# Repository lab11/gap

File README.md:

GAP: Generic Access Point
=========================
<div align="center">

</div>

GAP is the WiFi router for low-power and embedded Internet of Things devices.
While WiFi routers provide ubiquitous Internet access for laptops and
smartphones, GAP provides Internet access for low-power sensors and wearable
devices. It supports both 802.15.4 and Bluetooth Low Energy.

GAP is implemented as a cape for the
[BeagleBone Black](http://beagleboard.org/black). It uses two TI CC2520 radios
and a Nordic nRF51822 radio to provide connectivity. Each radio has a linux
kernel module to allow userspace access to the radios.

Hardware
--------

The GAP cape features a SPI interface to two CC2520
radios, one of which is amplified with a CC2591, and one nRF51822 radio.
It also includes four LEDs.

Software
--------

The CC2520 radios are
[supported natively](https://github.com/torvalds/linux/blob/master/drivers/net/ieee802154/cc2520.c)
in newer versions of the Linux kernel (>=4.1).

The nRF51822 BLE radio is a work-in-progress. It can be used as a standalone
BLE radio (see [this repo](https://github.com/lab11/nrf5x-base) for a starting
point), but does not have great integration with the BBB at this point.

Setting Up GAP
--------------

To setup a BBB to work with GAP, follow these instructions:

1. Start with a recent build of Debian for the BBB. We suggest starting
with pretty new version of Debian, like that can be found
[here](http://elinux.org/Beagleboard:BeagleBoneBlack_Debian#Jessie_Snapshot_console).

2. Once that is setup, ssh to the BBB and update the kernel to the newest
version. This will not only make sure you're running the latest code,
but also ensure all of the kernel modules will be present.

        sudo apt-get update
        sudo apt-get install vim git lsb-release
        sudo /opt/scripts/tools/update_kernel.sh --beta --bone-channel

    Luckily [Robert C Nelson](https://github.com/RobertCNelson/)
    has made this really easy with a convenient script.

3. Now we have to setup the device tree overlay to let Linux know that
the the radios exist. The GAP overlay and others are setup in a repository also
maintained by RCN.

        git clone https://github.com/lab11/bb.org-overlays
        cd bb.org-overlays
        ./dtc-overlay.sh
        ./install.sh

    That puts the compiled overlay in the correct place, now we need to tell
    the BBB to use it at boot.

        vim /boot/uEnv.txt
        # Edit that line that looks like this to include the reference to GAP
        cape_enable=bone_capemgr.enable_partno=BB-GAP

4. Reboot to apply this.

        sudo reboot

Sniffing 15.4 Packets
---------------------

To make sure everything is working, it is pretty easy to get Linux to
print out the packets the radio is receiving.

1. Install the `wpan-tools` to configure all of the 15.4 devices.

        sudo apt-get install pkg-config libnl-3-dev libnl-genl-3-dev
        wget http://wpan.cakelab.org/releases/wpan-tools-0.5.tar.gz
        tar xf wpan-tools-0.5.tar.gz
        cd wpan-tools-0.5
        ./configure
        make
        sudo make install

1. Install `tcpdump` to view the packets.

        sudo apt-get install tcpdump

2. Configure the network devices. Be sure to set the channel and PANID
to match what is transmitting the 15.4 packets.

        iwpan phy phy0 set channel 0 11
        iwpan dev wpan0 del
        iwpan phy phy0 interface add wpan0 type node c0:98:e5:00:00:00:00:01
        iwpan dev wpan0 set pan_id 0x0022
        /sbin/ifconfig wpan0 up

3. Use `tcpdump` to view them.

        sudo tcpdump -i wpan0 -vvv
        
    OR, use a simple c program to read from the raw socket.
    
        cd linux
        gcc recv_raw_802154.c -o raw
        sudo ./raw
        
    OR, use a very similar python script:
    
        cd linux
        sudo python recv_raw_802154.py

RPL Border Router
----------------

GAP can be setup as a border router running a 6LoWPAN based mesh network
with RPL as a routing layer. It uses [unstrung](https://github.com/mcr/unstrung)
to provide the RPL implementation. The rest is supported by the Linux kernel.

To set this up:

1. Setup the radios and network interfaces:

        sudo iwpan phy phy1 set channel 0 23
        sleep 15
        sudo iwpan dev wpan1 del
        sleep 15
        sudo iwpan phy phy1 interface add wpan1 type node c0:98:e5:00:00:00:00:01
        sleep 15
        sudo iwpan dev wpan1 set pan_id 0x0022
        sleep 15
        sudo ip link add link wpan1 name lowpan1 type lowpan
        sleep 15
        sudo ifconfig lowpan1 up
        sleep 15
        sudo ifconfig wpan1 up

   Note: I've found that putting a sleep between those commands makes everything run smoothly.
   Calling them too quickly seems to break things (at least in the past, it's possible
   that newer commits have solved this issue).

2. Get unstrung.

        git clone https://github.com/mcr/unstrung.git
        cd unstrung
        make

    There may be commits that need to be applied to make this
    work. Look at unstrung pull requests to see if there are
    outstanding patches that are required.

3. Run unstrung.

        /home/debian/unstrung/programs/sunshine/sunshine --verbose --dagid 0x11112222333344445555666677778888 -i lowpan1 -W 10000 --stderr -R 1 --prefix 2607:f018:800:201:c298:e588:4400:1/64 -m

4. You should be able to ping a node:

        sudo ping6 2607:f018:800:201:c298:e522:2200:bb -s 16

<!--

### Setup EEPROM

Now we are getting close. We have told Linux about the kernel modules
and added the device tree overlay to a place where Linux can find it.
The last step is to get Linux to load the overlay which will then cause
it to load the kernel modules. This is where the EEPROM comes in.

When the BeagleBone Black boots it checks for EEPROMs present on any capes
and uses the configuration data in the EEPROM to load the correct device
tree overlay.

There exists a utility to create the hexdump (data.eeprom) to flash to the
EEPROM in `/software/utility`. After creating the hexdump, apply a jumper
to the write header near the EEPROM chip and use this command to flash the
EEPROM:

Choose 12 characters to serve as the serial number, in
the form `WWYY&&&&nnnn`. From the SRM:

    WW = 2 digit week of the year of production.
    YY = 2 digit year of production.
    &&&& = Assembly code, up to you to decide.
    nnnn = incrementing board number for week of production.

After creating `data.eeprom` with the eepromflasher utilty, write it to the
cape EEPROM as root.

    # On the BBB
    sudo su
    cat data.eeprom > /sys/bus/i2c/devices/1-0057/eeprom

Where `1-0057` is the default address for the GAP cape. This can be changed
by using the solder jumper pads near the EEPROM on the upper left corner of the
board.

Unfortunately, the BBB debian distribution fails to load custom firmware from
the EEPROM on boot, and requires an capemanager configuration file to be
edited.

    sudo vim /etc/default/capemgr

    # Add this line:
    CAPE=BB-BONE-GAP

CC2520 Border Router
--------------------

One way to use the CC2520s on GAP is with the TinyOS code in a related
repo: [RaspberryPi-CC2520](https://github.com/lab11/raspberrypi-cc2520).
The `BorderRouter` application can be compiled with `make gap`.
-->

<!--

### EEPROM

The capes feature EEPROM that will allow for the BeagleBone capemgr to auto load the driver
and configure pins on boot, in accordance with the Beaglebone Black SRM. There
exists a utility to create the hexdump (data.eeprom) to flash to the EEPROM in
beaglebone-cc2520/software/utility. After creating the hexdump, apply a jumper
to the write header and use this command to flash the EEPROM:

```bash
cat data.eeprom > /sys/bus/i2c/devices/1-0057/eeprom
```

Where 1-0057 is the default address for the Zigbeag cape. This can be changed by
using the solder jumper pads on the upper left corner of the board.

Software
--------

### Install

This guide assumes the default Angstrom distro running under root.<br/>
Clone the repo to wherever you feel fit:

```bash
git clone https://github.com/lab11/beaglebone-cc2520.git
```

Note: you may have to follow the directions [here](http://derekmolloy.ie/fixing-git-and-curl-certificates-problem-on-beaglebone-blac/) to get git working correctly.

An install script is located in /software. <br/>
The script will copy the Device Tree Overlay (DTO) to /lib/firmware, and the driver to /lib/modules/KERNEL_VERSION, where KERNEL_VERSION is your current running kernel version number. <br/>
Navigate to software/ and run the install script:

```bash
cd beaglebone-cc2520/software/
./install
```

If using the Zigbeag cape with configured EEPROM, just plug it in and reboot the beaglebone and your board will be fully functional.

If EEPROM is not configured, to load the Device Tree Overlay manually:

```bash
echo BB-BONE-CC2520 > /sys/devices/bone_capemgr.9/slots
```
This command should complete with no output.
To check that the DTO has loaded, run:

```bash
cat /sys/devices/bone_capemgr.9/slots
```
Note: bone_capemgr.9 may actually be bone_capemgr.8 for different beaglebones. <br/>
You should check to see that there is now an override board in a slot after the virtual HDMI cape. <br/>
Here is my output:

```
 0: 54:PF---
 1: 55:PF---
 2: 56:PF---
 3: 57:PF---
 4: ff:P-O-L Bone-LT-eMMC-2G,00A0,Texas Instrument,BB-BONE-EMMC-2G
 5: ff:P-O-L Bone-Black-HDMI,00A0,Texas Instrument,BB-BONELT-HDMI
 7: ff:P-O-L Override Board Name,00A0,Override Manuf,BB-BONE-CC2520
```

Now that the DTO is loaded, the pins are now muxed correctly for the cc2520 board. We can now load the driver with:

```bash
modprobe cc2520
```

This command should complete with no output. <br/>
You can check that the driver loaded successfully with:

```bash
lsmod
```

#### Testing
You should now have a functioning Zigbeag cape. There are test programs located in software/driver/tests. Try running the write and read program on two beaglebones, and you should be able to see them talking to each other.

#### Install Issues
If you run into issues with any of the above commands, check dmesg for any output from the kernel. <br/>
Run this to check for issues with loading the DTO:

```bash
dmesg | grep bone_capemgr
```

Run this to check for issues with loading the driver:

```bash
dmesg | grep cc2520
```

### Kernel Module

In order to support the CC2520, you need the kernel module located in software/driver. The install script will automatically copy this into /lib/modules/KERNEL_VERSION. <br/>
This driver has been adapted from the [Linux CC2520 Driver](https:/github.com/ab500/linux-cc2520-driver). <br/>
If you would like to compile the driver from source, there is some setup involved.
I've found it easiest to use a symlink and compile from the current kernel on the Beaglebone.

```bash
opkg update
opkg upgrade
```
It would be a good idea to reboot at this point

```bash
opkg install kernel-headers
opkg install kernel-dev
cd /usr/src/kernel
make scripts
ln -s /usr/src/kernel /lib/modules/$(uname -r)/build
```

You can then navigate to beaglebone-cc2520/software/driver and run make to compile the driver. Make sure you re-run the install script, which will copy cc2520.ko to /lib/modules/KERNEL_VERSION and run depmod -a to register the driver with your system. -->

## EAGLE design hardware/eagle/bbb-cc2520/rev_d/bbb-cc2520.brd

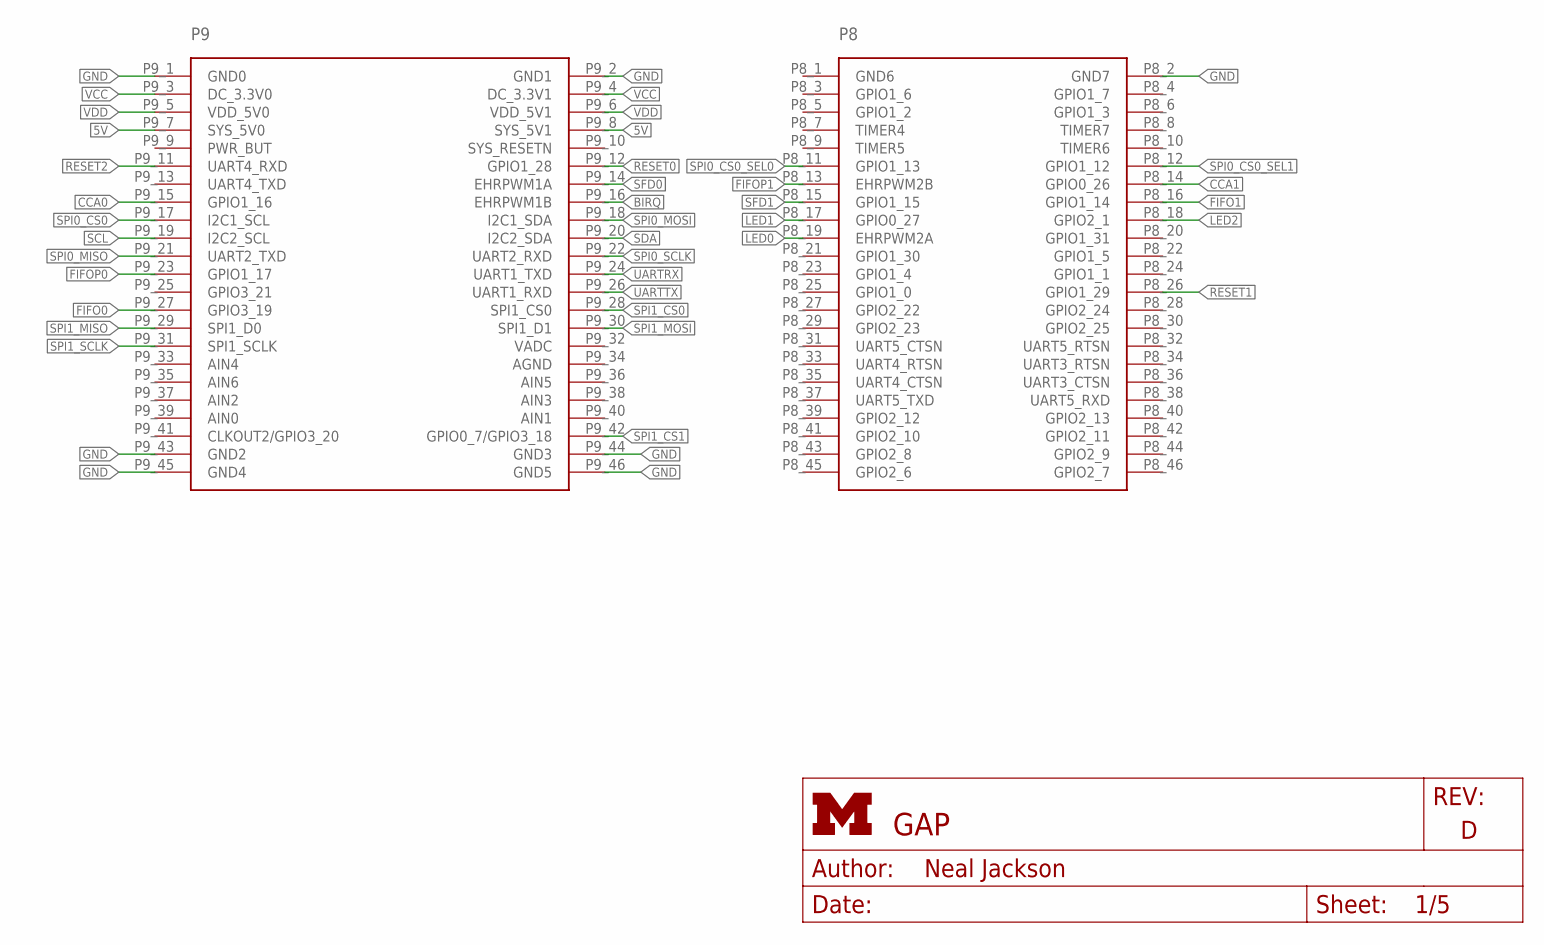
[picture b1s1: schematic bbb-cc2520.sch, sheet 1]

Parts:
P9/P8: BBB_HEADERS

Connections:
5V: P9/P8.P9_7 (SYS_5V0), P9/P8.P9_8 (SYS_5V1)
!RESET0: P9/P8.P9_12 (GPIO1_28); also elsewhere on the board
!RESET1: P9/P8.P8_26 (GPIO1_29); also elsewhere on the board
!RESET2: P9/P8.P9_11 (UART4_RXD); also elsewhere on the board
BIRQ: P9/P8.P9_16 (EHRPWM1B); also elsewhere on the board
CCA0: P9/P8.P9_15 (GPIO1_16); also elsewhere on the board
CCA1: P9/P8.P8_14 (GPIO0_26); also elsewhere on the board
FIFO0: P9/P8.P9_27 (GPIO3_19); also elsewhere on the board
FIFO1: P9/P8.P8_16 (GPIO1_14); also elsewhere on the board
FIFOP0: P9/P8.P9_23 (GPIO1_17); also elsewhere on the board
FIFOP1: P9/P8.P8_13 (EHRPWM2B); also elsewhere on the board
GND: P9/P8.P8_2 (GND7), P9/P8.P9_1 (GND0), P9/P8.P9_2 (GND1), P9/P8.P9_43 (GND2), P9/P8.P9_44 (GND3), P9/P8.P9_45 (GND4), P9/P8.P9_46 (GND5); also elsewhere on the board
LED0: P9/P8.P8_19 (EHRPWM2A); also elsewhere on the board
LED1: P9/P8.P8_17 (GPIO0_27); also elsewhere on the board
LED2: P9/P8.P8_18 (GPIO2_1); also elsewhere on the board
SCL: P9/P8.P9_19 (I2C2_SCL); also elsewhere on the board
SDA: P9/P8.P9_20 (I2C2_SDA); also elsewhere on the board
SFD0: P9/P8.P9_14 (EHRPWM1A); also elsewhere on the board
SFD1: P9/P8.P8_15 (GPIO1_15); also elsewhere on the board
SPI0_CS0: P9/P8.P9_17 (I2C1_SCL); also elsewhere on the board
SPI0_CS0_SEL0: P9/P8.P8_11 (GPIO1_13); also elsewhere on the board
SPI0_CS0_SEL1: P9/P8.P8_12 (GPIO1_12); also elsewhere on the board
SPI0_MISO: P9/P8.P9_21 (UART2_TXD); also elsewhere on the board
SPI0_MOSI: P9/P8.P9_18 (I2C1_SDA); also elsewhere on the board
SPI0_SCLK: P9/P8.P9_22 (UART2_RXD); also elsewhere on the board
SPI1_CS0: P9/P8.P9_28 (SPI1_CS0); also elsewhere on the board
SPI1_CS1: P9/P8.P9_42 (GPIO0_7/GPIO3_18); also elsewhere on the board
SPI1_MISO: P9/P8.P9_29 (SPI1_D0); also elsewhere on the board
SPI1_MOSI: P9/P8.P9_30 (SPI1_D1); also elsewhere on the board
SPI1_SCLK: P9/P8.P9_31 (SPI1_SCLK); also elsewhere on the board
UARTRX: P9/P8.P9_24 (UART1_TXD); also elsewhere on the board
UARTTX: P9/P8.P9_26 (UART1_RXD); also elsewhere on the board
VCC: P9/P8.P9_3 (DC_3.3V0), P9/P8.P9_4 (DC_3.3V1); also elsewhere on the board
VDD: P9/P8.P9_5 (VDD_5V0), P9/P8.P9_6 (VDD_5V1)

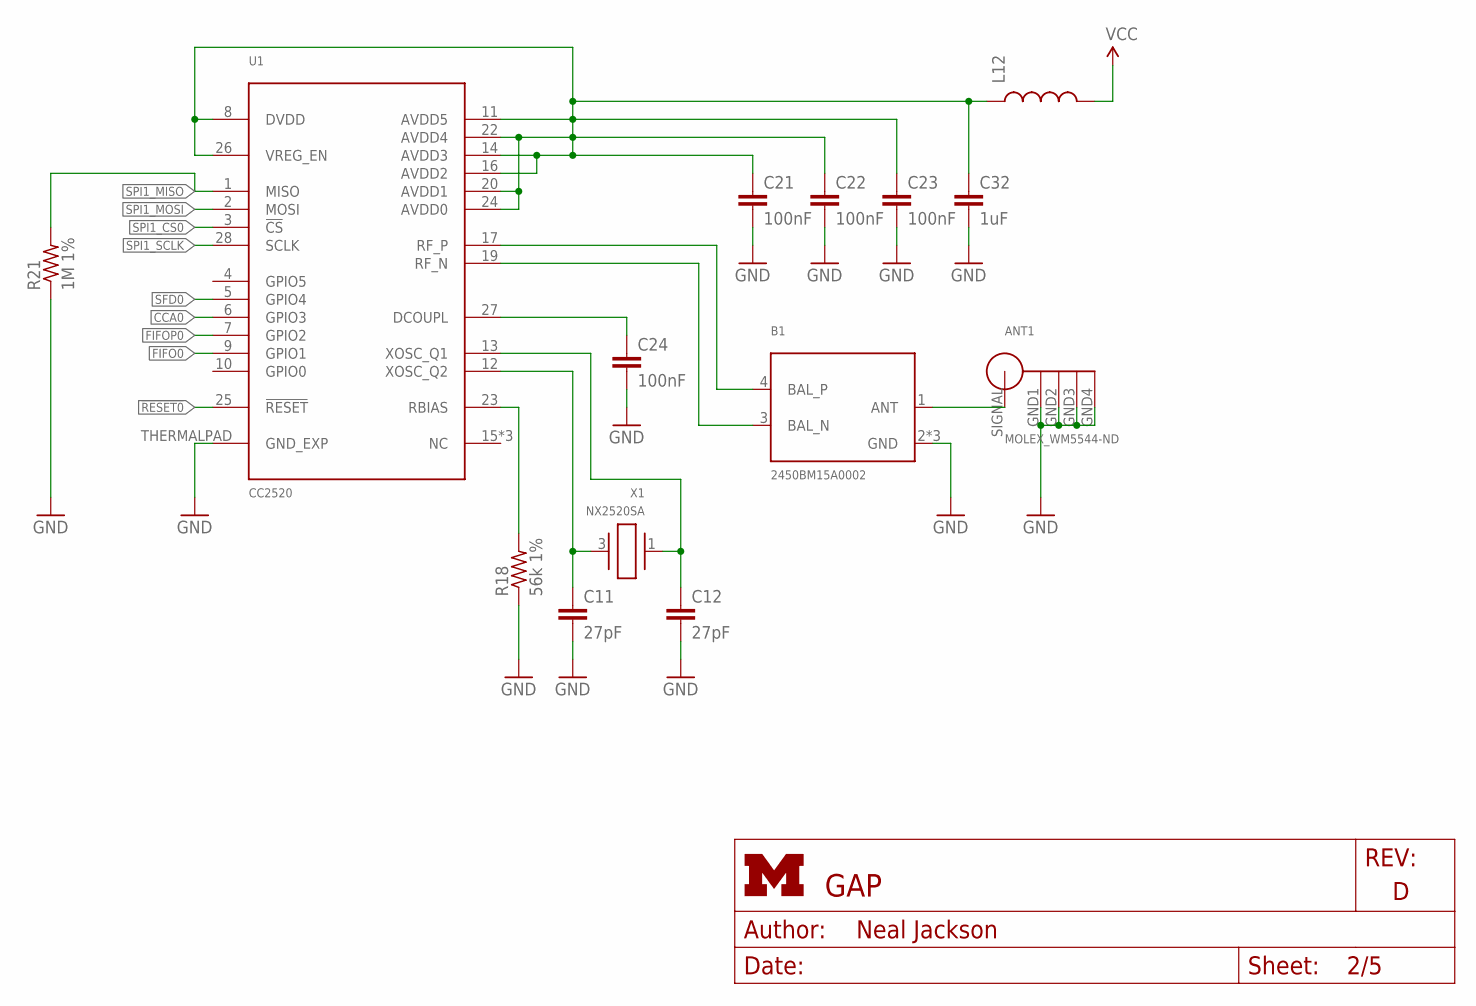
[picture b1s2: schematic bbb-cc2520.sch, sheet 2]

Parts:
ANT1: MOLEX_WM5544-ND
B1: 2450BM15A0002; 2450BM
C11, C12: 27pF; C0402; DIGIKEY 490-5869-1-ND
C21, C22, C23, C24: 100nF; C0402; DIGIKEY 490-1318-1-ND
C32: 1uF; C0603; DIGIKEY 490-1550-1-ND
L12: INDUCTOR0603; 0603; DIGIKEY 490-1015-1-ND
R18: 56k 1%; R0402; DIGIKEY P56.0KLCT-ND
R21: 1M 1%; R0402; DIGIKEY RHM1.00MCDCT-ND
U1: CC2520; S-PVQFN-N28
X1: NX2520SA

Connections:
!RESET0: U1.25 (!RESET); also elsewhere on the board
CCA0: U1.6 (GPIO3); also elsewhere on the board
FIFO0: U1.9 (GPIO1); also elsewhere on the board
FIFOP0: U1.7 (GPIO2); also elsewhere on the board
GND: ANT1.GND1, ANT1.GND2, ANT1.GND3, ANT1.GND4, B1.2 (GND), B1.5 (GND), B1.6 (GND), C11.2, C12.2, C21.2, C22.2, C23.2, C24.2, C32.2, R18.1, R21.1, U1.THERMALPAD (GND_EXP); also elsewhere on the board
unnamed: C21.1, C22.1, C23.1, C32.1, L12.1, U1.8 (DVDD), U1.11 (AVDD5), U1.14 (AVDD3), U1.16 (AVDD2), U1.20 (AVDD1), U1.22 (AVDD4), U1.24 (AVDD0), U1.26 (VREG_EN)
unnamed: ANT1.SIGNAL, B1.1 (ANT)
unnamed: C12.1, U1.13 (XOSC_Q1), X1.1
unnamed: C24.1, U1.27 (DCOUPL)
unnamed: C11.1, U1.12 (XOSC_Q2), X1.3 (2)
unnamed: R18.2, U1.23 (RBIAS)
RF_N: B1.3 (BAL_N), U1.19 (RF_N)
RF_P: B1.4 (BAL_P), U1.17 (RF_P)
SFD0: U1.5 (GPIO4); also elsewhere on the board
SPI1_CS0: U1.3 (!CS); also elsewhere on the board
SPI1_MISO: R21.2, U1.1 (MISO); also elsewhere on the board
SPI1_MOSI: U1.2 (MOSI); also elsewhere on the board
SPI1_SCLK: U1.28 (SCLK); also elsewhere on the board
VCC: L12.2; also elsewhere on the board

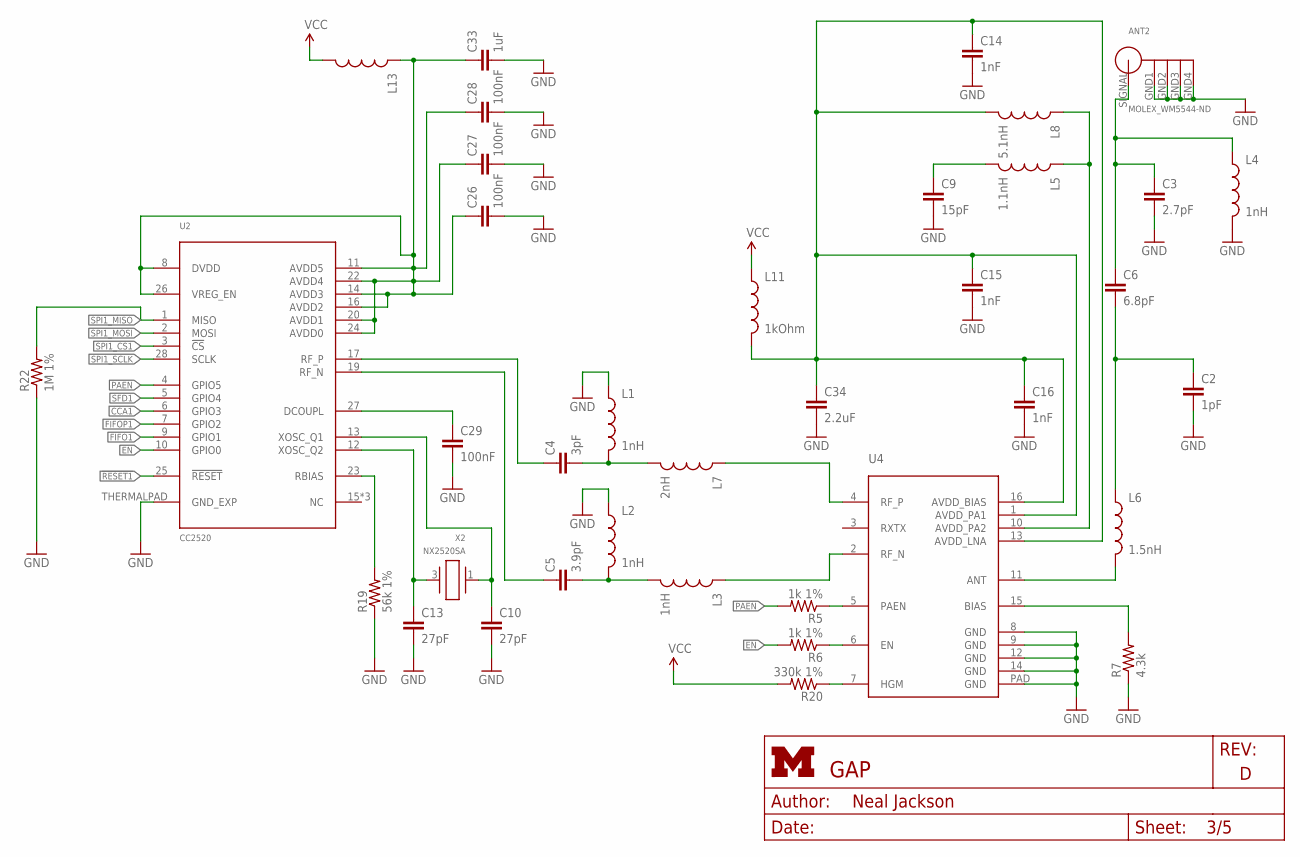
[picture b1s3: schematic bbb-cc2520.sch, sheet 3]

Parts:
ANT2: MOLEX_WM5544-ND
C2: 1pF; C0402; DIGIKEY 490-1318-1-ND
C3: 2.7pF; C0402; DIGIKEY 490-1318-1-ND
C4: 3pF; C0402; DIGIKEY 490-1318-1-ND
C5: 3.9pF; C0402; DIGIKEY 490-1318-1-ND
C6: 6.8pF; C0402; DIGIKEY 490-1318-1-ND
C9: 15pF; C0402; DIGIKEY 490-1318-1-ND
C10, C13: 27pF; C0402; DIGIKEY 490-5869-1-ND
C14, C15, C16: 1nF; C0402; DIGIKEY 490-1318-1-ND
C26, C27, C28, C29: 100nF; C0402; DIGIKEY 490-1318-1-ND
C33: 1uF; C0603; DIGIKEY 490-1550-1-ND
C34: 2.2uF; C0402; DIGIKEY 490-1318-1-ND
L1, L2, L3, L4: 1nH; C0402
L5: 1.1nH; C0402
L6: 1.5nH; C0402
L7: 2nH; C0402
L8: 5.1nH; C0402
L11: 1kOhm; C0402
L13: INDUCTOR0603; 0603; DIGIKEY 490-1015-1-ND
R5, R6: 1k 1%; R0402; DIGIKEY P56.0KLCT-ND
R7: 4.3k; R0402; DIGIKEY P56.0KLCT-ND
R19: 56k 1%; R0402; DIGIKEY P56.0KLCT-ND
R20: 330k 1%; R0402; DIGIKEY P56.0KLCT-ND
R22: 1M 1%; R0402; DIGIKEY RHM1.00MCDCT-ND
U2: CC2520; S-PVQFN-N28
U4: CC2591; PVQFN-16
X2: NX2520SA

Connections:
!RESET1: U2.25 (!RESET); also elsewhere on the board
CCA1: U2.6 (GPIO3); also elsewhere on the board
EN: R6.2, U2.10 (GPIO0)
FIFO1: U2.9 (GPIO1); also elsewhere on the board
FIFOP1: U2.7 (GPIO2); also elsewhere on the board
GND: ANT2.GND1, ANT2.GND2, ANT2.GND3, ANT2.GND4, C2.2, C3.2, C9.2, C10.2, C13.2, C14.2, C15.2, C16.2, C26.2, C27.2, C28.2, C29.2, C33.2, C34.2, L1.1, L2.1, L4.2, R7.1, R19.1, R22.1, U2.THERMALPAD (GND_EXP), U4.8 (GND), U4.9 (GND), U4.12 (GND), U4.14 (GND), U4.PAD (GND); also elsewhere on the board
unnamed: L7.1, U4.4 (RF_P)
unnamed: L3.1, U4.2 (RF_N)
unnamed: C5.2, L2.2, L3.2
unnamed: C4.2, L1.2, L7.2
unnamed: L5.1, L8.1, U4.10 (AVDD_PA2)
unnamed: C14.1, C15.1, C16.1, C34.1, L8.2, L11.2, U4.1 (AVDD_PA1), U4.13 (AVDD_LNA), U4.16 (AVDD_BIAS)
unnamed: C9.1, L5.2
unnamed: L6.2, U4.11 (ANT)
unnamed: ANT2.SIGNAL, C3.1, C6.1, L4.1
unnamed: C2.1, C6.2, L6.1
unnamed: R7.2, U4.15 (BIAS)
unnamed: R5.1, U4.5 (PAEN)
unnamed: R6.1, U4.6 (EN)
unnamed: C26.1, C27.1, C28.1, C33.1, L13.1, U2.8 (DVDD), U2.11 (AVDD5), U2.14 (AVDD3), U2.16 (AVDD2), U2.20 (AVDD1), U2.22 (AVDD4), U2.24 (AVDD0), U2.26 (VREG_EN)
unnamed: C29.1, U2.27 (DCOUPL)
unnamed: C10.1, U2.13 (XOSC_Q1), X2.1
unnamed: C13.1, U2.12 (XOSC_Q2), X2.3 (2)
unnamed: R19.2, U2.23 (RBIAS)
unnamed: R20.1, U4.7 (HGM)
PAEN: R5.2, U2.4 (GPIO5)
RF_N2: C5.1, U2.19 (RF_N)
RF_P2: C4.1, U2.17 (RF_P)
SFD1: U2.5 (GPIO4); also elsewhere on the board
SPI1_CS1: U2.3 (!CS); also elsewhere on the board
SPI1_MISO: R22.2, U2.1 (MISO); also elsewhere on the board
SPI1_MOSI: U2.2 (MOSI); also elsewhere on the board
SPI1_SCLK: U2.28 (SCLK); also elsewhere on the board
VCC: L11.1, L13.2, R20.2; also elsewhere on the board

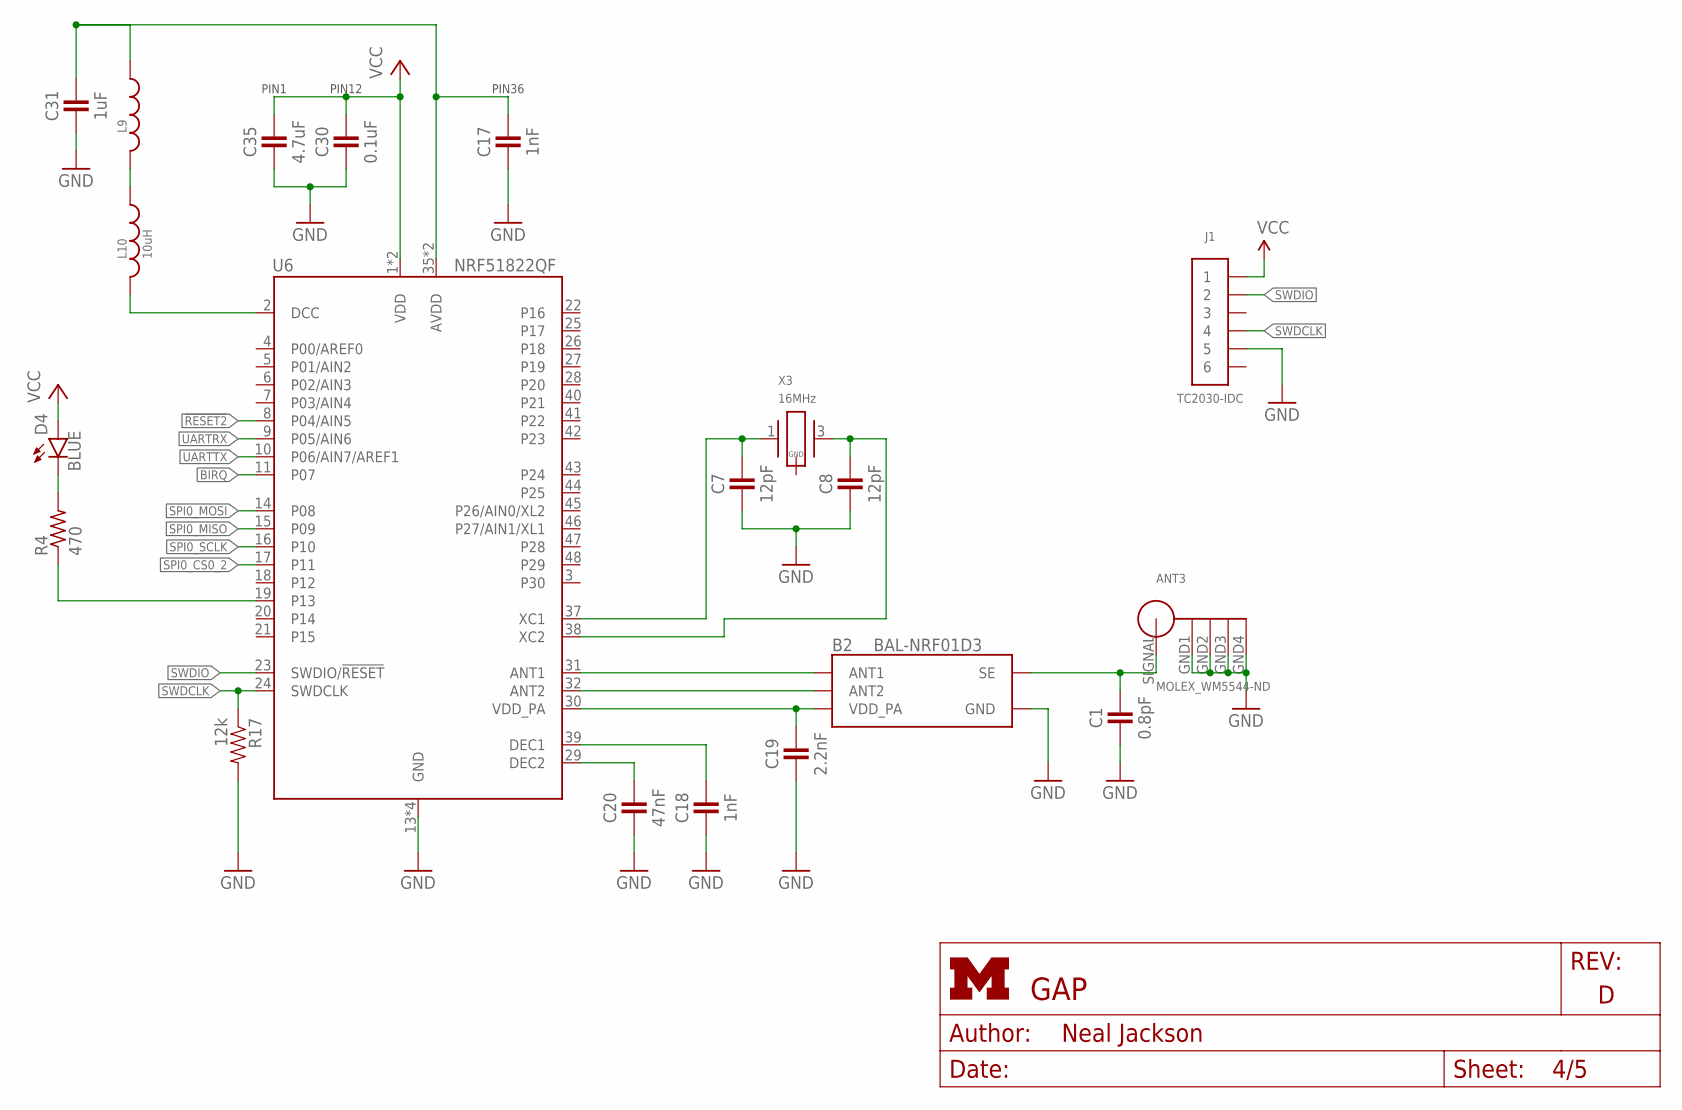
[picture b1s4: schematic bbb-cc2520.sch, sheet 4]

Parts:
ANT3: MOLEX_WM5544-ND
B2: BAL-NRF01D3
C1: 0.8pF; 0402_CAP; DIGIKEY 490-5419-1-ND
C7, C8: 12pF; 0402_CAP; DIGIKEY 490-6197-1-ND
C17, C18: 1nF; 0402_CAP; DIGIKEY 490-1303-1-ND
C19: 2.2nF; 0402_CAP; DIGIKEY 490-5419-1-ND
C20: 47nF; 0402_CAP; DIGIKEY 445-1264-1-ND
C30: 0.1uF; 0402_CAP; DIGIKEY 445-4952-1-ND
C31: 1uF; 0402_CAP; DIGIKEY 1276-1513-1-ND
C35: 4.7uF; 0402_CAP; DIGIKEY 445-5947-1-ND
D4: BLUE; LED-0603
J1: TC2030-IDC
L9: INDUCTOR0402; 0402_CAP; DIGIKEY 587-1521-1-ND
L10: 10uH; 0603_CAP; DIGIKEY 490-4025-1-ND
R4: 470; R0402; DIGIKEY RHM470JCT-ND
R17: 12k; 0603-RES; DIGIKEY RHM12.0KCDCT-ND
U6: NRF51822QF; QFN-48-6MM
X3: 16MHz; TXC-8Y; DIGIKEY 887-2003-1-ND

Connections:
!RESET2: U6.8 (P04/AIN5); also elsewhere on the board
AVDD: C17.1, C31.1, L9.1, U6.35 (AVDD), U6.36 (AVDD)
BIRQ: U6.11 (P07); also elsewhere on the board
DCC: L10.2, U6.2 (DCC)
GND: ANT3.GND1, ANT3.GND2, ANT3.GND3, ANT3.GND4, B2.GND, C1.2, C7.2, C8.2, C17.2, C18.2, C19.2, C20.2, C30.2, C31.2, C35.2, J1.5, R17.2, U6.13 (GND), U6.33 (GND), U6.34 (GND), U6.GND; also elsewhere on the board
unnamed: B2.ANT1, U6.31 (ANT1)
unnamed: B2.ANT2, U6.32 (ANT2)
unnamed: ANT3.SIGNAL, B2.SE, C1.1
unnamed: L9.2, L10.1
unnamed: C7.1, U6.37 (XC1), X3.1
unnamed: C8.1, U6.38 (XC2), X3.3 (2)
unnamed: C18.1, U6.39 (DEC1)
unnamed: C20.1, U6.29 (DEC2)
unnamed: D4.C, R4.2
unnamed: R4.1, U6.19 (P13)
SPI0_CS0_2: U6.17 (P11); also elsewhere on the board
SPI0_MISO: U6.15 (P09); also elsewhere on the board
SPI0_MOSI: U6.14 (P08); also elsewhere on the board
SPI0_SCLK: U6.16 (P10); also elsewhere on the board
SWDCLK: J1.4, R17.1, U6.24 (SWDCLK)
SWDIO: J1.2, U6.23 (SWDIO/!RESET)
UARTRX: U6.9 (P05/AIN6); also elsewhere on the board
UARTTX: U6.10 (P06/AIN7/AREF1); also elsewhere on the board
VCC: C30.1, C35.1, D4.A, J1.1, U6.1 (VDD), U6.12 (VDD); also elsewhere on the board
VDD_PA: B2.VCC (VDD_PA), C19.1, U6.30 (VDD_PA)

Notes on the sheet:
PIN12
PIN1
PIN36

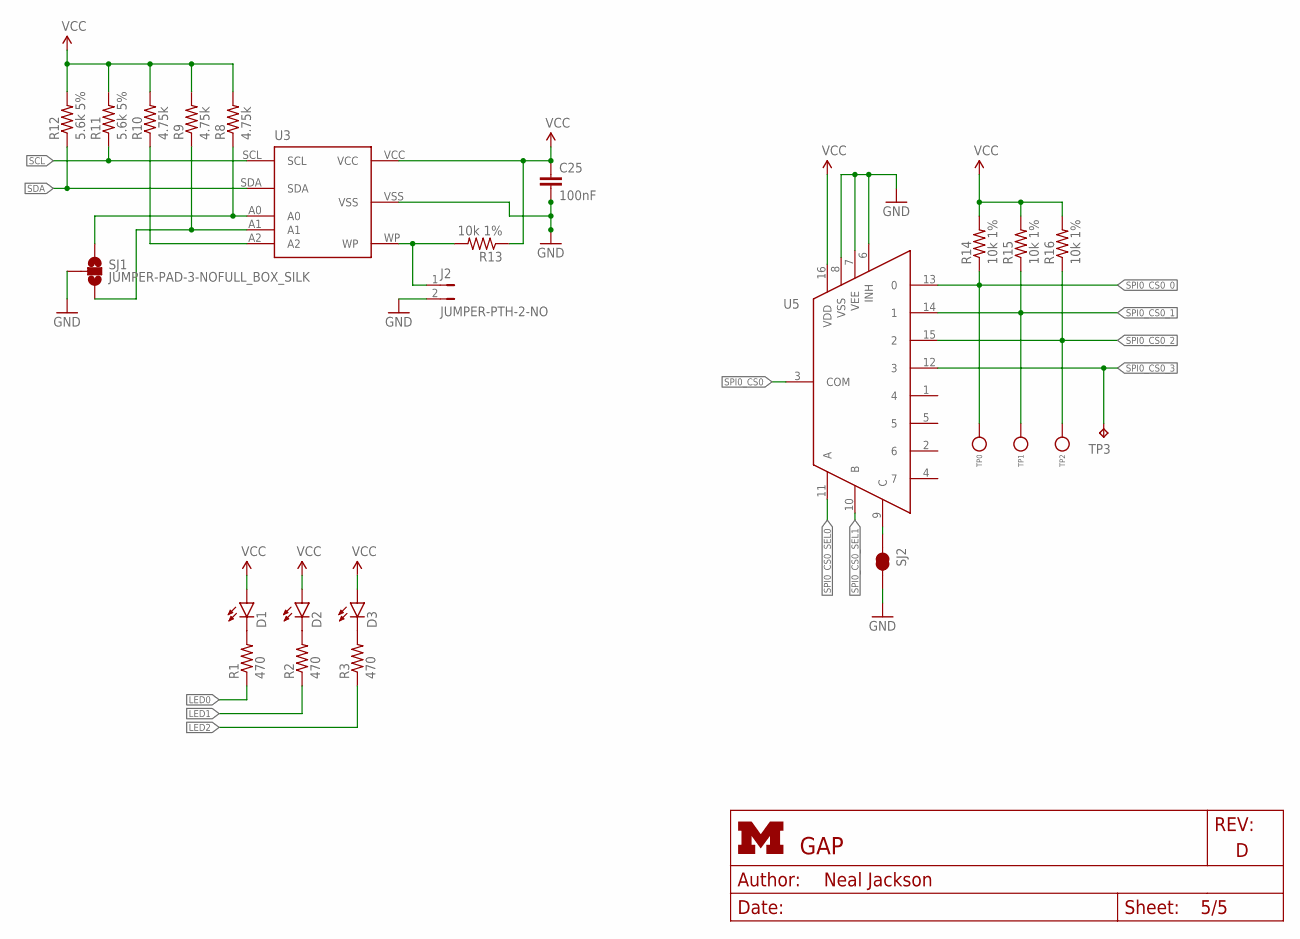
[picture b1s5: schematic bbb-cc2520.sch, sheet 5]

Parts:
C25: 100nF; C0402; DIGIKEY 490-1318-1-ND
D1: LED0603; LED-0603; DIGIKEY 160-1834-1-ND
D2: LED0603; LED-0603; DIGIKEY 160-1835-1-ND
D3: LED0603; LED-0603; DIGIKEY 160-1837-1-ND
J2: JUMPER-PTH-2-NO; PTH-JUMPER-2-NO_NO_SILK
R1, R2, R3: 470; R0402; DIGIKEY RHM470JCT-ND
R8, R9, R10: 4.75k; R0402; DIGIKEY RHM1.00MCDCT-ND
R11, R12: 5.6k 5%; R0402; DIGIKEY RHM1.00MCDCT-ND
R13, R14, R15, R16: 10k 1%; R0402; DIGIKEY RHM1.00MCDCT-ND
SJ1: JUMPER-PAD-3-NOFULL_BOX_SILK; PAD-JUMPER-3-NO_YES_SILK_FULL_BOX
SJ2: JUMPER-PAD-2-NC_BY_TRACE; PAD-JUMPER-2-NC_BY_TRACE_YES_SILK
TP0, TP1, TP2: TEST_POINT_0.040IN; TESTPOINT_0.040IN
TP3: TPTP14SQ; TP14SQ
U3: CAT24C256WI-GT3
U5: CD4051B-53B; TSSOP16

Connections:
GND: C25.2, J2.2, SJ1.2, SJ2.2, U3.VSS, U5.6 (INH), U5.7 (VEE), U5.8 (VSS); also elsewhere on the board
LED0: R1.1; also elsewhere on the board
LED1: R2.1; also elsewhere on the board
LED2: R3.1; also elsewhere on the board
unnamed: D1.C, R1.2
unnamed: D2.C, R2.2
unnamed: D3.C, R3.2
unnamed: R8.1, SJ1.1, U3.A0
unnamed: R9.1, SJ1.3, U3.A1
unnamed: J2.1, R13.2, U3.WP
unnamed: R10.1, U3.A2
unnamed: SJ2.1, U5.9 (C)
SCL: R11.1, U3.SCL; also elsewhere on the board
SDA: R12.1, U3.SDA; also elsewhere on the board
SPI0_CS0: U5.3 (COM); also elsewhere on the board
SPI0_CS0_0: R14.1, TP0.TESTPOINT, U5.13 (0)
SPI0_CS0_1: R15.1, TP1.TESTPOINT, U5.14 (1)
SPI0_CS0_2: R16.1, TP2.TESTPOINT, U5.15 (2); also elsewhere on the board
SPI0_CS0_3: TP3.TP, U5.12 (3)
SPI0_CS0_SEL0: U5.11 (A); also elsewhere on the board
SPI0_CS0_SEL1: U5.10 (B); also elsewhere on the board
VCC: C25.1, D1.A, D2.A, D3.A, R8.2, R9.2, R10.2, R11.2, R12.2, R13.1, R14.2, R15.2, R16.2, U3.VCC, U5.16 (VDD); also elsewhere on the board

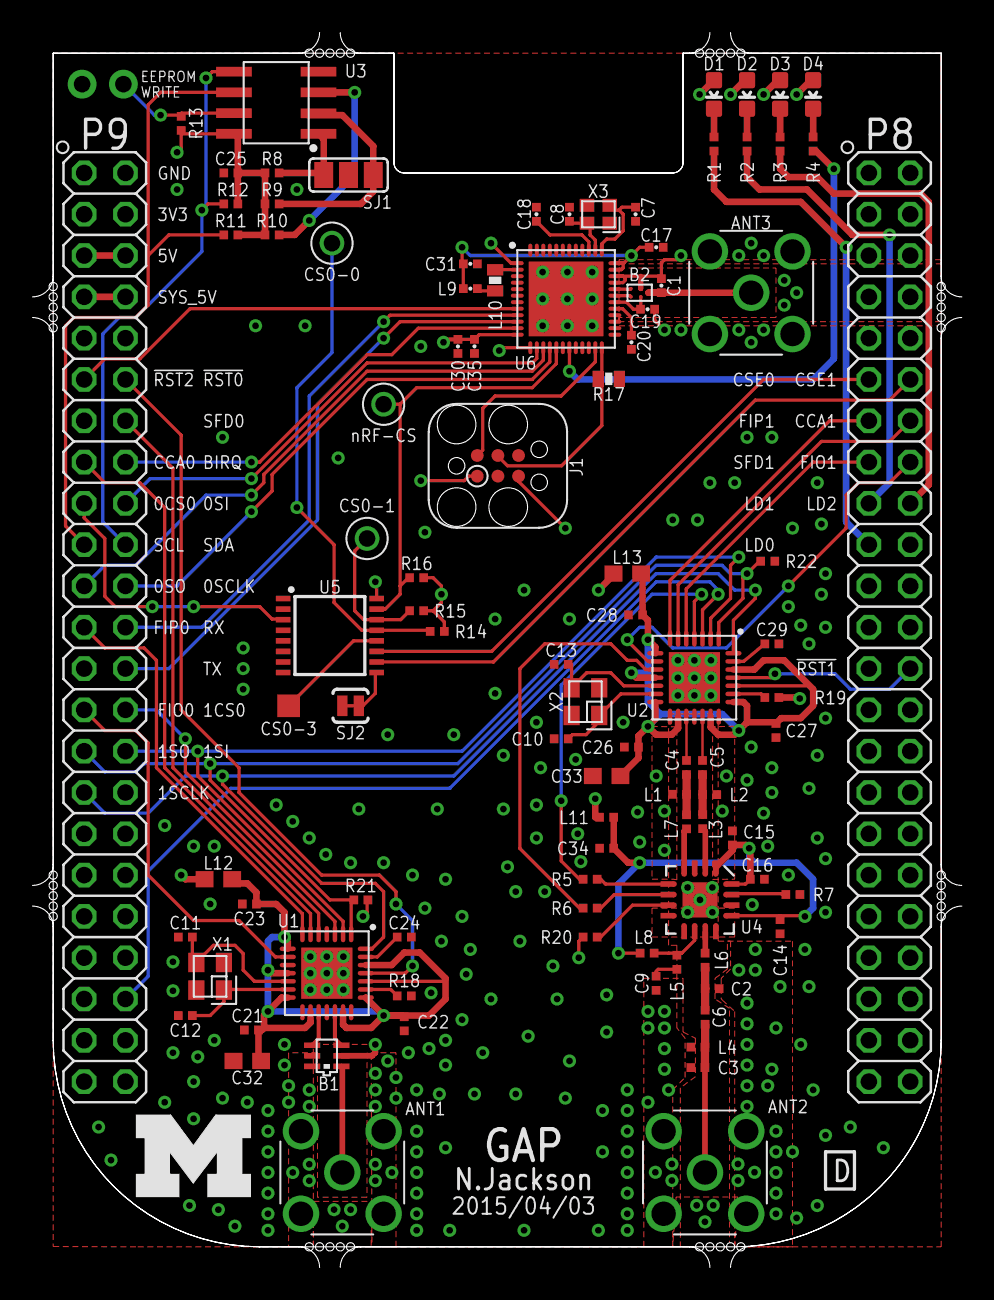
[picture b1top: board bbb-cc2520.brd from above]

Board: 4 copper layers, 57.2 x 75.9 mm, 98 parts (0 on the bottom side), 92 nets.

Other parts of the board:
U$2: UMICH_SOLID_200MIL

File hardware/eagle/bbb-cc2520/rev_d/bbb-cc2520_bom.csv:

Qty,Value,Device,Package,Parts,Description,DIGIKEY,SAMTEC,MAJOR LEAGUE
3,MOLEX_WM5544-ND,MOLEX_WM5544-ND,MOLEX_WM5544-ND,"ANT1, ANT2, ANT3",Through-hole SMA Antenna,WM5544-ND,,
1,2450BM15A0002,2450BM15A0002,2450BM,B1,BALUN JTI MATCHED ZIGBEE,712-1536-1-ND,,
1,BAL-NRF01D3,BAL-NRF01D3,BAL-NRF01D3,B2,"50 ohm nominal input / conjugate match balun to nRF51422-QFAA,",497-13637-1-ND,,
1,0.8pF,CAPACITOR,0402_CAP,C1,0402 Capacitor,490-6269-1-ND,,
1,1pF,C-EUC0402,C0402,C2,"Capacitor, 1p, 0402, NP0, +/-0.1pF 50V",490-6206-1-ND,,
1,2.7pF,C-EUC0402,C0402,C3,"Capacitor, 2p7, 0402, NP0, +-0.25pF, 50V",490-5934-1-ND,,
1,3pF,C-EUC0402,C0402,C4,"Capacitor, 3p, 0402, NP0, +-0.25pF, 50V",490-5872-1-ND,,
1,3.9pF,C-EUC0402,C0402,C5,"Capacitor, 3p9, 0402, NP0, +-0.25pF, 50V",490-1272-1-ND,,
1,6.8pF,C-EUC0402,C0402,C6,"Capacitor, 6p8, 0402, NP0, +-0.25pF 50V",490-5949-1-ND,,
2,12pF,CAPACITOR,0402_CAP,"C7, C8",0402 Capacitor,490-6197-1-ND,,
1,15pF,C-EUC0402,C0402,C9,"Capacitor, 15p, 0402, NP0, 5%, 50V",490-5888-1-ND,,
4,27pF,C-EUC0402,C0402,"C10, C11, C12, C13","Capacitor, 27p, 0402, NP0, 5%, 50V",490-5869-1-ND,,
3,1nF,C-EUC0402,C0402,"C14, C15, C16","Capacitor, 1n, 0402, NP0, 5%, 50V",490-3244-1-ND,,
2,1nF,CAPACITOR,0402_CAP,"C17, C18",0402 Capacitor,490-1303-1-ND,,
1,2.2nF,CAPACITOR,0402_CAP,C19,0402 Capacitor,490-5419-1-ND,,
1,47nF,CAPACITOR,0402_CAP,C20,0402 Capacitor,445-1264-1-ND,,
9,100nF,C-EUC0402,C0402,"C21, C22, C23, C24, C25, C26, C27, C28, C29","Capacitor, 100n, 0402, X5R, 10%, 10V",490-1318-1-ND,,
1,0.1uF,CAPACITOR,0402_CAP,C30,0402 Capacitor,445-4952-1-ND,,
1,1uF,CAPACITOR,0402_CAP,C31,0402 Capacitor,1276-1513-1-ND,,
2,1uF,C-EUC0603,C0603,"C32, C33","Capacitor, 1u0, 0603, X5R, 10%, 6.3V",490-1550-1-ND,,
1,2.2uF,C-EUC0402,C0402,C34,"Capacitor, 2u2, 0402, X5R, 20%, 4V",490-4518-1-ND,,
1,4.7uF,CAPACITOR,0402_CAP,C35,0402 Capacitor,445-5947-1-ND,,
1,GREEN,LED0603,LED-0603,D1,LEDs,160-1834-1-ND,,
1,RED,LED0603,LED-0603,D2,LEDs,160-1835-1-ND,,
1,BLUE,LED0603,LED-0603,D3,LEDs,160-1837-1-ND,,
1,YELLOW,LED0603,LED-0603,D4,LEDs,160-1831-1-ND,,
1,JUMPER-PTH-2-NO,JUMPER-PTH-2-NO,PTH-JUMPER-2-NO_NO_SILK,J2,,3M9447-ND,,
4,1nH,INDUCTOR0402,C0402,"L1, L2, L3, L4","Inductor, 1n0, 0402, Monolithic type, +/-0.3 nH",490-2610-1-ND,,
1,1.1nH,INDUCTOR0402,C0402,L5,"Inductor, 1n1, 0402, Monolithic type, +/-0.3 nH",490-6567-1-ND,,
1,1.5nH,INDUCTOR0402,C0402,L6,"Inductor, 1n5, 0402, wire-wound type, +/-0.1 nH",490-6782-1-ND,,
1,2nH,INDUCTOR0402,C0402,L7,"Inductor, 2n0, 0402, +/-0.3 nH",490-6569-1-ND,,
1,5.1nH,INDUCTOR0402,C0402,L8,"Inductor, 5n1, 0402, +/-0.3 nH",490-6573-1-ND,,
1,15nH,INDUCTOR0402,0402_CAP,L9,,587-1521-1-ND,,
1,10uH,INDUCTOR0603,0603_CAP,L10,,490-4025-1-ND,,
1,1k Ohm,INDUCTOR0402,C0402,L11,"EMI filter bead, 0402 1Kohms GHz Band Gen Use",490-3999-1-ND,,
2,1k Ohm,INDUCTOR0603,L0603,"L12, L13","EMI filter bead, 0603 1Kohms GHz Band Gen Use",490-1015-1-ND,,
2,BBB_HEADERS,BBB_HEADERS,BBB_HEADERS,"P8, P9",2x23 Pin Header,,SSQ-123-03-T-D,SSHQ-123-D-08-G-LF
4,470 ohm,R-US_R0402,R0402,"R1, R2, R3, R4","RESISTOR, American symbol",RHM470CDCT-ND,,
2,1k 1%,R-US_R0402,R0402,"R5, R6","RESISTOR, American symbol",RHM1.00KCDCT-ND,,
1,4.3k,R-US_R0402,R0402,R7,"RESISTOR, American symbol",1276-4078-1-ND,,
3,4.75k,R-US_R0402,R0402,"R8, R9, R10","RESISTOR, American symbol",1276-4083-1-ND,,
2,5.6k 5%,R-US_R0402,R0402,"R11, R12","RESISTOR, American symbol",RHM5.6KCECT-ND,,
4,10k 1%,R-US_R0402,R0402,"R13, R14, R15, R16","RESISTOR, American symbol",RHM10.0KCDCT-ND,,
1,12k,RESISTOR,0603-RES,R17,Resistor,RHM12.0KCDCT-ND,,
2,56k 1%,R-US_R0402,R0402,"R18, R19","RESISTOR, American symbol",P56.0KLCT-ND,,
1,330k 1%,R-US_R0402,R0402,R20,"RESISTOR, American symbol",RHM330KCFCT-ND,,
2,1M 1%,R-US_R0402,R0402,"R21, R22","RESISTOR, American symbol",RHM1.00MCDCT-ND,,
3,TEST_POINT_0.040IN,TEST_POINT_0.040IN,TESTPOINT_0.040IN,"TP0, TP1, TP2",0.040in Test Point,5001K-ND,,
2,CC2520,CC2520,S-PVQFN-N28,"U1, U2",2.4 GHZ IEEE 802.15.4/ZIGBEE® RF TRANSCEIVER,296-22996-1-ND,,
1,CAT24C256WI-GT3,CAT24C256WI-GT3,SOIC-8,U3,256kb Serial CMOS EEPROM,CAT24C256WI-GT3OSCT-ND,,
1,CC2591,CC2591,PVQFN-16,U4,2.4GHz Range Extender,296-23603-1-ND,,
1,CD4051B-53B,CD4051B-53B,TSSOP16,U5,IC MUX/DEMUX 8x1 16TSSOP,296-11993-1-ND,,
1,NRF51822QF,NRF51822QF,QFN-48-6MM,U6,Multiprotocol Bluetooth® 4.0 low energy/2.4 GHz RF SoC 32kB/256kB,1490-1042-1-ND,,
2,NX2520SA,NX2520SA,NX2520SA,"X1, X2",CRYSTAL 32MHZ 10PF SMD,644-1065-1-ND,,
1,16MHz,TXC-8Y,TXC-8Y,X3,2mmx1.6mm SMD Crystal,887-2003-1-ND,,

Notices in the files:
software/overlay/BB-BONE-GAP.dts:
Copyright (C) 2014 Neal Jackson, LAB11
This program is free software; you can redistribute it and/or modify
it under the terms of the GNU General Public License version 2 as
published by the Free Software Foundation.
parts and their libraries:
SparkFun-LED: Licensing: CC v3.0 Share-Alike You are welcome to use this library for commercial purposes.
SparkFun-Aesthetics: Licensing: Creative Commons ShareAlike 4.0 International - https://creativecommons.org/licenses/by-sa/4.0
